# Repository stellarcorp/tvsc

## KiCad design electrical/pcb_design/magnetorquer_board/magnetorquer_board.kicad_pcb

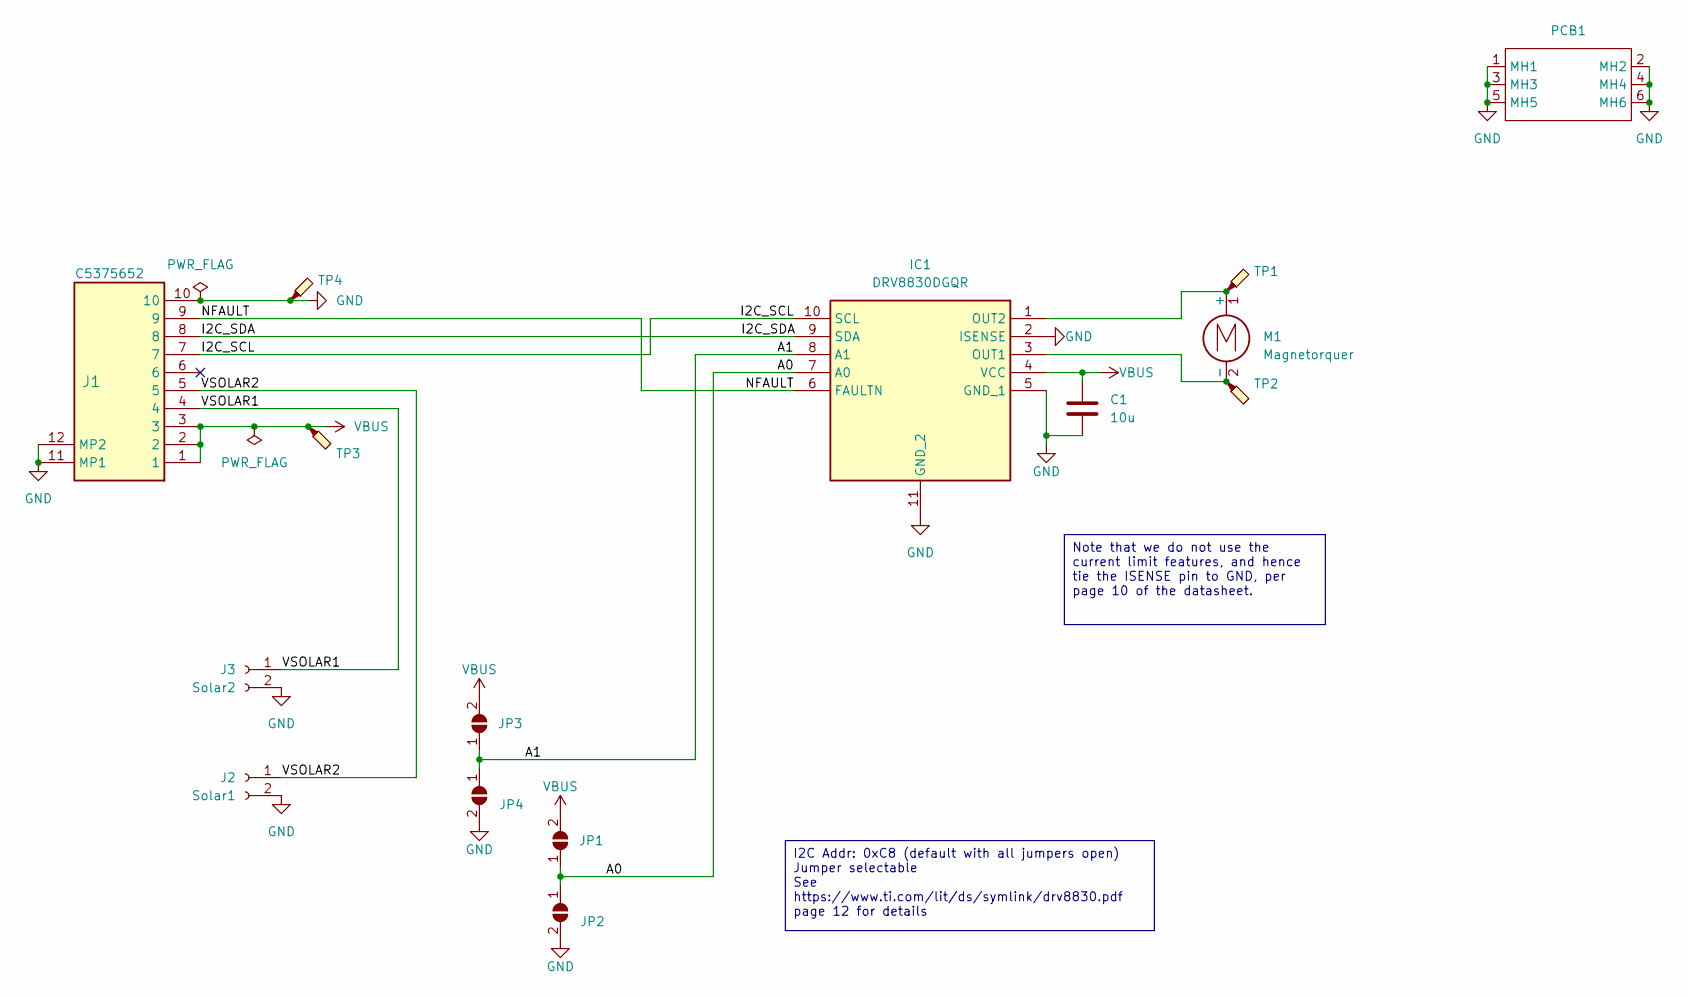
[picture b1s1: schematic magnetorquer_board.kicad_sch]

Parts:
C1: 10u; C_1206_3216Metric; MPN C77093
IC1: DRV8830DGQR; SOP50P490X110-11N; MPN C127591
J1: Molex_504050-0891; Molex_504050-1091; MPN C5375652
J2: Solar1; Solar Panel Connector (Raw Pads); MPN NA
J3: Solar2; Solar Panel Connector (Raw Pads); MPN NA
JP1, JP2, JP3, JP4: SolderJumper_2_Open; SolderJumper-2_P1.3mm_Open_RoundedPad1.0x1.5mm; MPN NA
M1: Magnetorquer; MPN NA
PCB1: Interior_Side_Panel_PCB_Shape; MPN NA
TP1, TP2, TP3, TP4: TestPoint_Probe; TestPoint_Pad_D1.5mm; MPN NA

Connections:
/A0: IC1.7 (A0), JP1.1 (A), JP2.1 (A)
/A1: IC1.8 (A1), JP3.1 (A), JP4.1 (A)
/I2C_SCL: IC1.10 (SCL), J1.7
/I2C_SDA: IC1.9 (SDA), J1.8
/NFAULT: IC1.6 (FAULTN), J1.9
/VSOLAR1: J1.4, J3.1
/VSOLAR2: J1.5, J2.1
GND: C1.2, IC1.2 (ISENSE), IC1.5 (GND_1), IC1.11 (GND_2), J1.10, J1.11 (MP1), J1.12 (MP2), J2.2, J3.2, JP2.2 (B), JP4.2 (B), PCB1.1 (MH1), PCB1.2 (MH2), PCB1.3 (MH3), PCB1.4 (MH4), PCB1.5 (MH5), PCB1.6 (MH6), TP4.1
unnamed: IC1.3 (OUT1), M1.2 (-), TP2.1
unnamed: IC1.1 (OUT2), M1.1 (+), TP1.1
VBUS: C1.1, IC1.4 (VCC), J1.1, J1.2, J1.3, JP1.2 (B), JP3.2 (B), TP3.1

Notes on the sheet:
Note that we do not use the current limit features, and hence tie the ISENSE pin to GND, per page 10 of the datasheet.
I2C Addr: 0xC8 (default with all jumpers open) Jumper selectable See https://www.ti.com/lit/ds/symlink/drv8830.pdf page 12 for details

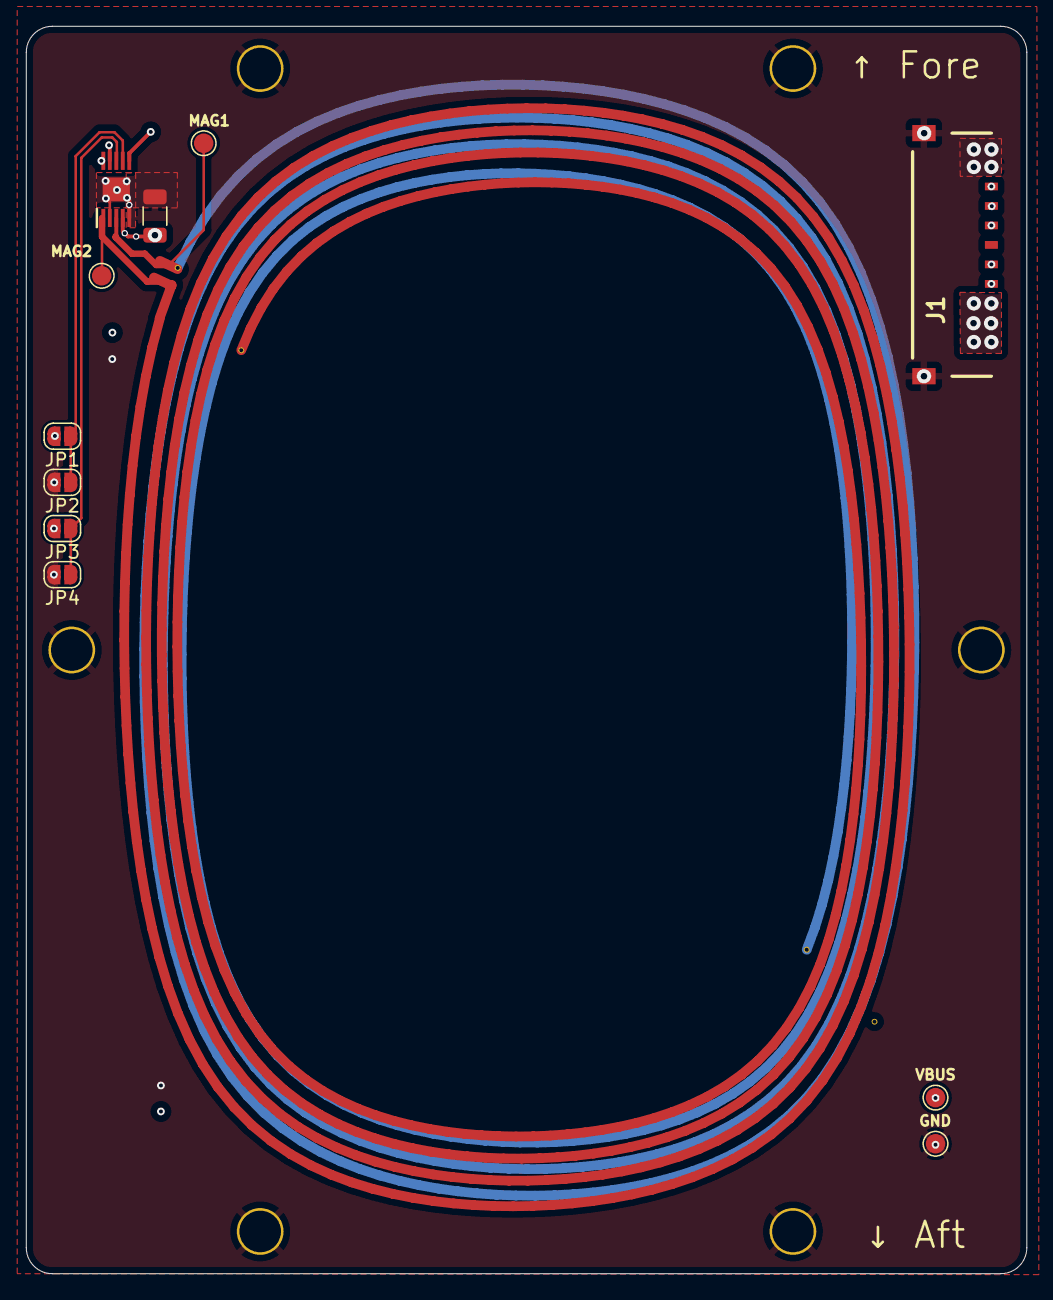
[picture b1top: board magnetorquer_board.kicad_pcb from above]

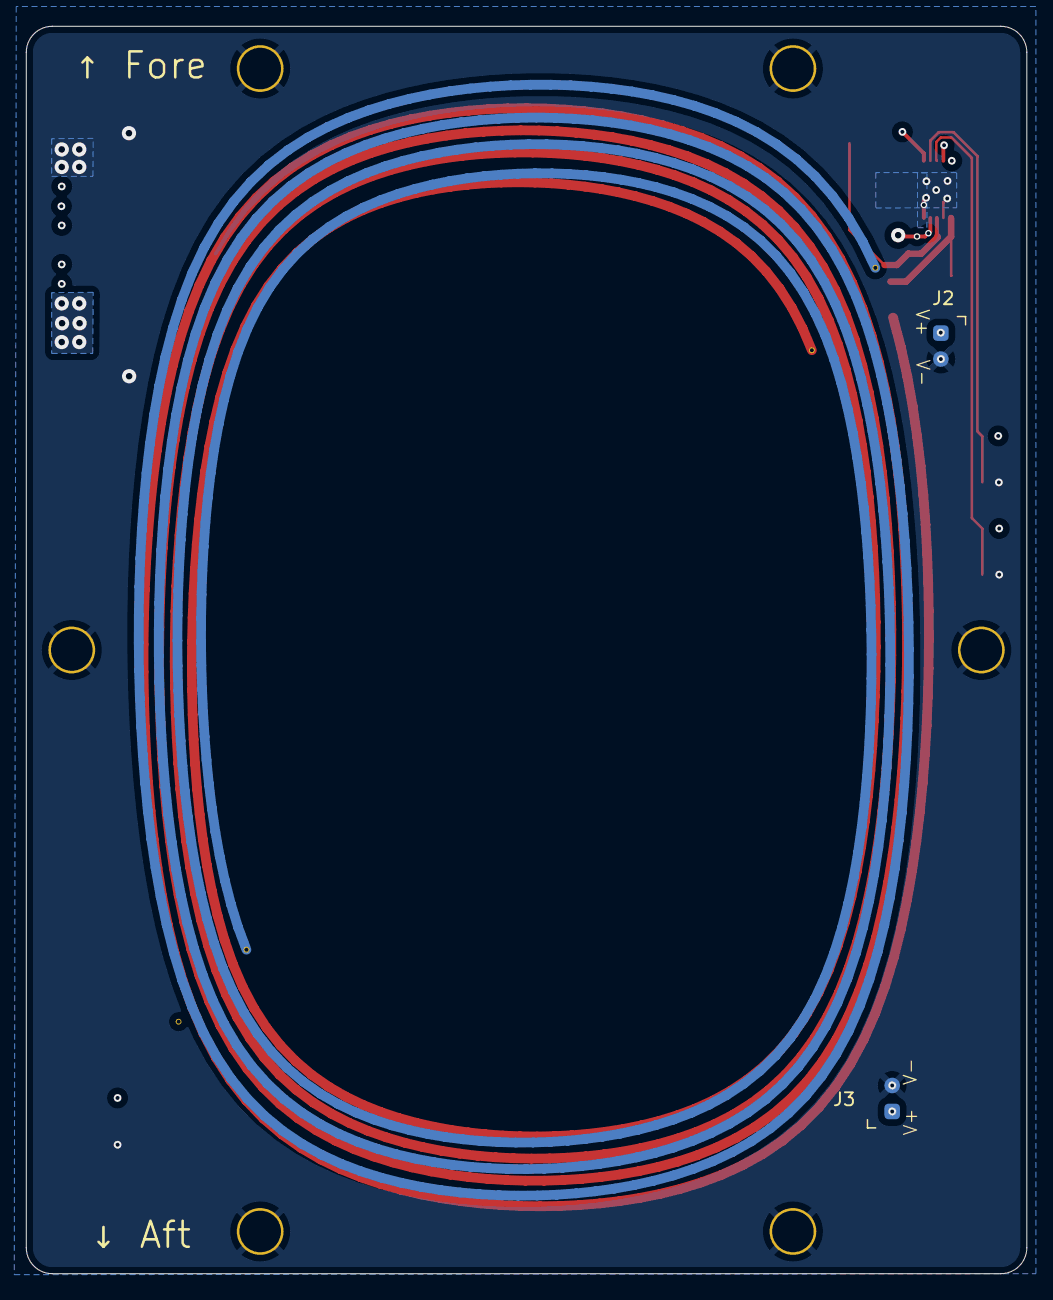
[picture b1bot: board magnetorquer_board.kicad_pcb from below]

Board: 4 copper layers, 77.0 x 96.0 mm, 15 parts (2 on the bottom side), 11 nets.

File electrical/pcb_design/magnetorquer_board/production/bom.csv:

Designator,Footprint,Quantity,Value,LCSC Part #
C1,1206,1,10u,C77093
IC1,SOP50P490X110-11N,1,DRV8830DGQR,C127591
J1,Molex_504050-0891,1,Molex_504050-0891,C587992
J2,Solar Panel Connector (Raw Pads),1,Solar1,NA
J3,Solar Panel Connector (Raw Pads),1,Solar2,NA
"JP1, JP2, JP3, JP4",SolderJumper-2_P1.3mm_Open_RoundedPad1.0x1.5mm,4,SolderJumper_2_Open,NA
M1,Magnetorquer,1,Magnetorquer,NA
"TP1, TP2, TP3, TP4",TestPoint_Pad_D1.5mm,4,TestPoint_Probe,NA

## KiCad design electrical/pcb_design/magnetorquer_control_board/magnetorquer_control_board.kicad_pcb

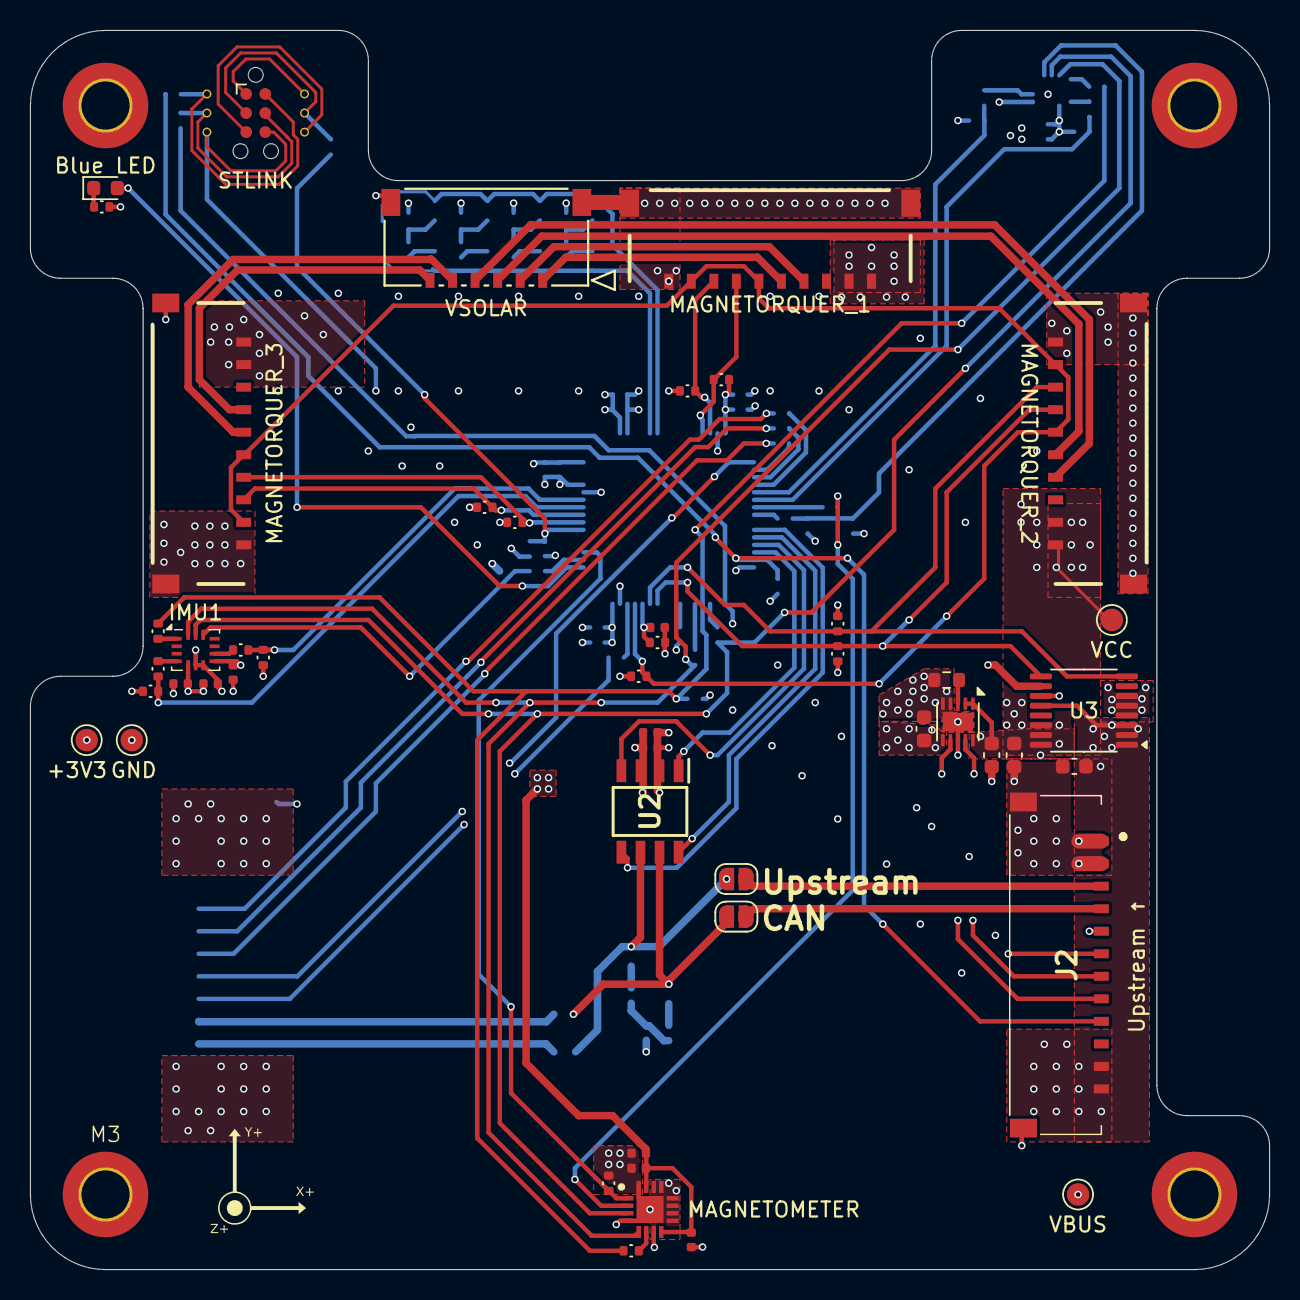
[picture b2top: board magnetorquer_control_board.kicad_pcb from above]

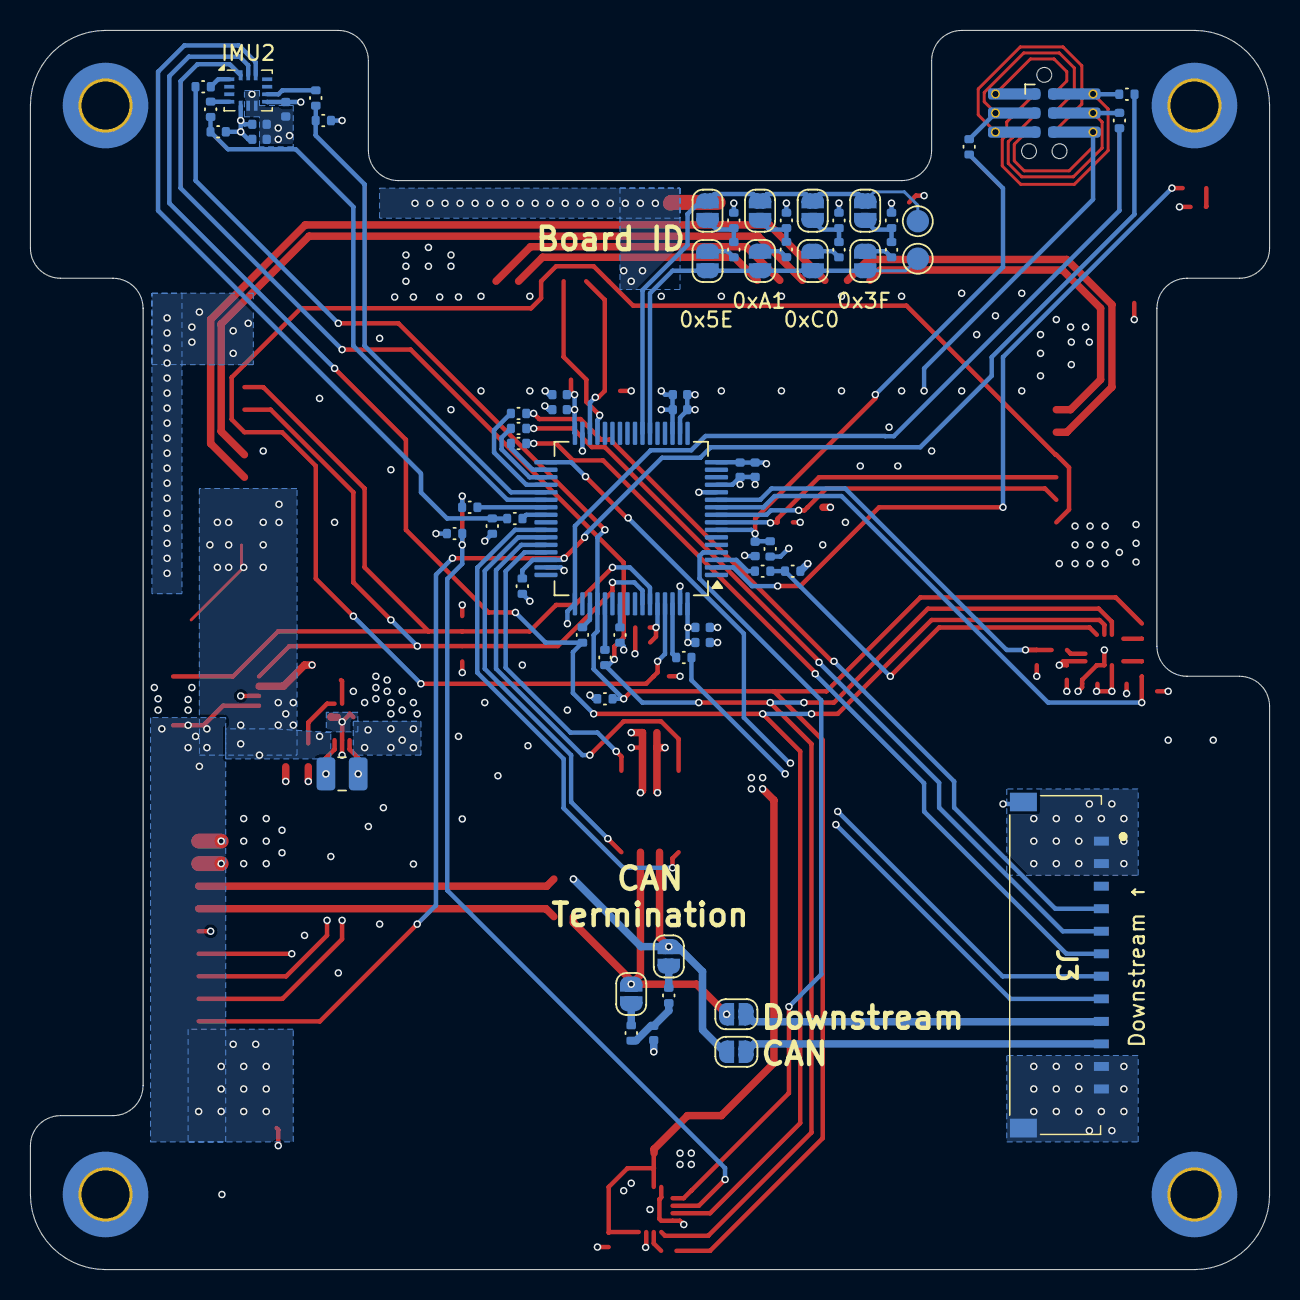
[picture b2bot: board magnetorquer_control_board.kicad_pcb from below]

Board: 4 copper layers, 82.5 x 82.5 mm, 114 parts (66 on the bottom side), 86 nets.

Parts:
C1, C2, C3, C7, C8, C9, C13, C14, C17, C18, C21, C22, C23, C25: 100n; Nondescript_C_0402_1005Metric
C4, C26: 10u; Nondescript_C_0603_1608Metric
C5, C27: 22u; Nondescript_C_0603_1608Metric
C10, C11, C12, C15, C16, C19, C20, C24: 1u; Nondescript_C_0402_1005Metric
D1: Blue LED; LED_0603_1608Metric
J1: STLINK; Double-Sided_Tag-Connect_TC2030-IDC-NL_2x03_P1.27mm_Vertical
J2: Molex_504050-1291; Bus Connector (Target)
J3: Molex_504050-1291; Bus Connector (Control)
J4: VSOLAR; Molex_504050-0691
J5: MAGNETORQUER_1; Molex_504050-1091
J6: MAGNETORQUER_2; Molex_504050-1091
J7: MAGNETORQUER_3; Molex_504050-1091
JP1, JP2, JP3, JP4, JP5, JP6: SolderJumper_2_Open; SolderJumper-2_P1.3mm_Open_RoundedPad1.0x1.5mm
JP7, JP11: 0x3F; SolderJumper-2_P1.3mm_Open_RoundedPad1.0x1.5mm
JP8, JP12: 0xC0; SolderJumper-2_P1.3mm_Open_RoundedPad1.0x1.5mm
JP9, JP13: 0xA1; SolderJumper-2_P1.3mm_Open_RoundedPad1.0x1.5mm
JP10, JP14: 0x5E; SolderJumper-2_P1.3mm_Open_RoundedPad1.0x1.5mm
L1: 2.2µH; L_1008_2520Metric
PCB1: Core_Board_Shape_Space_Invader_2
R1, R3, R6, R10, R11, R12, R13, R14, R15, R16, R22, R25, R29, R32, R33, R34, R35, R36, R44, R47, R48: 9k31; Nondescript_R_0402_1005Metric
R2, R4, R5, R7, R8, R9, R17, R18, R19, R20, R21, R23, R24, R26, R27, R28, R30, R31, R37, R38, R39: 33; Nondescript_R_0402_1005Metric
R40, R43: 18k7; Nondescript_R_0402_1005Metric
R41, R42: 6k19; Nondescript_R_0402_1005Metric
R45, R46: 15k8; Nondescript_R_0402_1005Metric
R49, R50: 60; Nondescript_R_0402_1005Metric
R51: 36k5; Nondescript_R_0603_1608Metric
TP1: VBUS; TestPoint_Pad_D1.5mm
TP2: VCC; TestPoint_Pad_D1.5mm
TP3: GND; TestPoint_Pad_D1.5mm
TP4: +3V3; TestPoint_Pad_D1.5mm
TP5: BOARD_ID_SENSE; TestPoint_Pad_D1.5mm
TP6: BOARD_ID_POWER; TestPoint_Pad_D1.5mm
U1: STM32L452RCTx; LQFP-64_10x10mm_P0.5mm
U2: TCAN330DR; SOIC127P600X175-8N
U3: INA260; TSSOP-16_4.4x5mm_P0.65mm
U5: MAGNETOMETER; QFN50P300X300X100-17N-D
U6: IMU1; Bosch_LGA-14_3x2.5mm_P0.5mm
U7: IMU2; Bosch_LGA-14_3x2.5mm_P0.5mm
U8: TPS63900; WSON-10-1EP_2.5x2.5mm_P0.5mm_EP1.2x2mm

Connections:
+3V3: C5.1, C7.1, C8.1, C9.1, C10.1, C11.1, C12.1, C13.1, C14.1, C15.1, C16.1, C17.1, C18.1, C19.1, C20.1, C21.1, C22.1, C23.1, C24.1, C25.1, J1.1 (T_VCC), R1.1, R6.1, R10.1, R11.1, R12.1, R13.1, R14.1, R15.1, R16.1, R22.1, R25.1, R29.1, R32.1, R33.1, R35.1, R36.1, R48.1, TP4.1, U1.13 (VDDA), U1.19 (VDD), U1.32 (VDD), U1.64 (VDD), U2.3 (VCC), U3.10 (VS), U5.8 (VDD_IO), U5.15 (VDD), U6.5 (VDDIO), U6.8 (VDD), U7.5 (VDDIO), U7.8 (VDD), U8.6 (VOUT)
/BOOT0: C2.1, J2.5 (BOOT0), R3.1, U1.60 (PH3)
/Board Identification/BOARD_ID_POWER: JP11.1 (A), JP12.1 (A), JP13.1 (A), JP14.1 (A), TP6.1, U1.22 (PA6)
/Board Identification/BOARD_ID_SENSE: JP7.1 (A), JP8.1 (A), JP9.1 (A), JP10.1 (A), TP5.1, U1.23 (PA7)
/CAN bus/CANH_TERMINATION: JP3.2 (B), R49.1
/CAN bus/CANL_TERMINATION: JP4.1 (A), R50.2
/CAN bus/CAN_RX: U1.44 (PA11), U2.4 (RXD)
/CAN bus/CAN_SHUTDOWN: U1.42 (PA9), U2.5 (SHDN)
/CAN bus/CAN_SILENT: U1.43 (PA10), U2.8 (S)
/CAN bus/CAN_TX: U1.45 (PA12), U2.1 (TXD)
/CANH_DOWNSTREAM: J3.9 (CANH), JP5.2 (B)
/CANH_UPSTREAM: J2.4 (CANH), JP1.1 (A)
/CANL_DOWNSTREAM: J3.10 (CANL), JP6.2 (B)
/CANL_UPSTREAM: J2.3 (CANL), JP2.1 (A)
/CTRL.BOOT0: J3.8 (BOOT0_CTRL), R7.2
/CTRL.NRST: J3.5 (NRST_CTRL), R5.2
/CTRL.SWCLK: J3.6 (SWCLK_CTRL), R8.2
/CTRL.SWDIO: J3.4 (SWDIO_CTRL), R9.2
/CTRL.SWO: J3.7 (SWO_CTRL), U1.33 (PB12)
/I2C1.SCL: J6.4, R12.2, U1.58 (PB6), U3.9 (SCL)
/I2C1.SDA: J6.3, R11.2, U1.59 (PB7), U3.8 (SDA)
/I2C2.SCL: J5.4, R14.2, U1.29 (PB10)
/I2C2.SDA: J5.3, R13.2, U1.30 (PB11)
/I2C3.SCL: J7.4, R16.2, U1.8 (PC0)
/I2C3.SDA: J7.3, R15.2, U1.9 (PC1)
/IMU/IMU1_INT1: R26.2, R35.2, U1.10 (PC2)
/IMU/IMU1_INT2: R27.2, R32.2, U1.11 (PC3)
/IMU/IMU1_SPI_CS: R21.1, R48.2, U6.12 (CSB)
/IMU/IMU2_INT1: R30.2, R36.2, U1.38 (PC7)
/IMU/IMU2_INT2: R31.2, R33.2, U1.37 (PC6)
/IMU/IMU2_SPI_CS: R20.1, R29.2, U7.12 (CSB)
/IMU/IMU_MAG_INT1: R34.1, U1.4 (PC15), U5.1 (INT)
/IMU/IMU_MAG_SPI_CS: R17.1, R25.2, U5.2 (SENB/CS)
/MCU/DEBUG_LED: D1.2 (A), U1.2 (PC13)
/MCU/NMAG_FAULT: J5.2, J5.5, J6.2, J6.5, J7.2, J7.5, R10.2, U1.61 (PB8)
/Magnetorquer Control/VSOLAR_1_1: J4.1, J5.6
/Magnetorquer Control/VSOLAR_1_2: J4.2, J5.7
/Magnetorquer Control/VSOLAR_2_1: J4.3, J6.6
/Magnetorquer Control/VSOLAR_2_2: J4.4, J6.7
/Magnetorquer Control/VSOLAR_3_1: J4.5, J7.6
/Magnetorquer Control/VSOLAR_3_2: J4.6, J7.7
/NRST: C1.1, J2.8 (NRST), R1.2, R37.1, U1.7 (NRST)
/SPI3.MISO: R22.2, R23.2, R24.1, R28.2, U1.52 (PC11)
/SPI3.MOSI: R19.1, U5.5 (SDA/MOSI), U6.14 (SDx), U7.14 (SDx)
/SPI3.SCK: R18.1, U5.3 (SCL/SCLK), U6.13 (SCx), U7.13 (SCx)
/SWCLK: J2.7 (SWCLK), R39.1, U1.49 (PA14)
/SWDIO: J2.9 (SWDIO), R6.2, R38.1, U1.46 (PA13)
/SWO: J1.6 (T_SWO), J2.6 (SWO), R4.2
GND: C1.2, C2.2, C3.1, C4.2, C5.2, C7.2, C8.2, C9.2, C10.2, C11.2, C12.2, C13.2, C14.2, C15.2, C16.2, C17.2, C18.2, C19.2, C20.2, C21.2, C22.2, C23.2, C24.2, C25.2, C26.2, C27.2, J1.5 (GND), J2.1 (GND), J2.2 (GND), J2.MP1, J2.MP2, J3.11 (GND), J3.12 (GND), J3.MP1, J3.MP2, J4.7 (MP1), J4.8 (MP2), J5.1, J5.11 (MP1), J5.12 (MP2), J6.1, J6.11 (MP1), J6.12 (MP2), J7.1, J7.11 (MP1), J7.12 (MP2), PCB1.MH1, PCB1.MH2, PCB1.MH3, PCB1.MH4, R2.2, R3.2, R34.2, R41.2, R43.2, R45.1, R47.1, R51.2, TP3.1, U1.12 (VSSA), U1.16 (PA2), U1.18 (VSS), U1.31 (VSS), U1.47 (VSS), U1.63 (VSS), U2.2 (GND), U3.4 (A1), U3.5 (A0), U3.6 (GND), U3.11 (GND), U5.4 (N/C_1), U5.7 (INT/TRIG), U5.9 (N/C_2), U5.10 (N/C_3), U5.11 (A1), U5.12 (A0), U5.13 (VSS), U5.14 (N/C_4), U5.16 (N/C_5), U5.17 (EP), U6.6 (GNDIO), U6.7 (GND), U7.6 (GNDIO), U7.7 (GND), U8.4 (CFG2), U8.5 (CFG3), U8.8 (GND), U8.11 (GND)
unnamed: C3.2, R49.2, R50.1
unnamed: D1.1 (K), R2.1
unnamed: J1.3 (T_NRST), R37.2
unnamed: J1.4 (T_SWCLK), R39.2
unnamed: J1.2 (T_SWDIO), R38.2
unnamed: JP1.2 (B), JP3.1 (A), JP5.1 (A), U2.7 (CANH)
unnamed: JP2.2 (B), JP4.2 (B), JP6.1 (A), U2.6 (CANL)
unnamed: JP7.2 (B), R40.2, R41.1
unnamed: JP8.2 (B), R42.2, R43.1
unnamed: JP9.2 (B), R44.1, R45.2
unnamed: JP10.2 (B), R46.1, R47.2
unnamed: JP11.2 (B), R40.1
unnamed: JP12.2 (B), R42.1
unnamed: JP13.2 (B), R44.2
unnamed: JP14.2 (B), R46.2
unnamed: R4.1, U1.55 (PB3)
unnamed: R7.1, U1.62 (PB9)
unnamed: R8.1, U1.34 (PB13)
unnamed: R5.1, U1.35 (PB14)
unnamed: R9.1, U1.36 (PB15)
unnamed: R17.2, U1.39 (PC8)
unnamed: R20.2, U1.40 (PC9)
unnamed: R18.2, U1.51 (PC10)
unnamed: R19.2, U1.53 (PC12)
unnamed: R21.2, U1.3 (PC14)
unnamed: R23.1, U5.6 (MISO)
unnamed: R26.1, U6.4 (INT1)
unnamed: R27.1, U6.9 (INT2)
unnamed: R24.2, U6.1 (SDO)
unnamed: R30.1, U7.4 (INT1)
unnamed: R31.1, U7.9 (INT2)
unnamed: R28.1, U7.1 (SDO)
unnamed: R51.1, U8.3 (CFG1)
unnamed: L1.2, U8.9 (LX1)
unnamed: L1.1, U8.7 (LX2)
VBUS: C4.1, J2.11 (VBUS), J2.12 (VBUS), J3.1 (VBUS), J3.2 (VBUS), TP1.1, U3.1 (IN+), U3.2 (IN+), U3.3 (IN+), U3.12 (VBUS)
VCC: C26.1, C27.1, J5.9, J5.10, J6.9, J6.10, J7.9, J7.10, TP2.1, U3.14 (IN-), U3.15 (IN-), U3.16 (IN-), U8.1 (EN), U8.2 (SEL), U8.10 (VIN)

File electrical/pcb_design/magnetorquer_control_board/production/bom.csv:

Designator,Footprint,Quantity,Value,LCSC Part #
"C1, C13, C14, C17, C18, C2, C21, C22, C23, C25, C3, C7, C8, C9",Nondescript_C_0402_1005Metric,14,100n,C1525
"C10, C11, C12, C15, C16, C19, C20, C24",Nondescript_C_0402_1005Metric,8,1u,C52923
"C26, C4",Nondescript_C_0603_1608Metric,2,10u,C77041
"C27, C5",Nondescript_C_0603_1608Metric,2,22u,C710887
D1,0603,1,Blue LED,C72041
J2,Bus Connector (Target),1,Molex_504050-1291,C563982
J3,Bus Connector (Control),1,Molex_504050-1291,C563982
J4,Molex_504050-0691,1,VSOLAR,C563981
J5,Molex_504050-1091,1,MAGNETORQUER_1,C5375652
J6,Molex_504050-1091,1,MAGNETORQUER_2,C5375652
J7,Molex_504050-1091,1,MAGNETORQUER_3,C5375652
L1,1008,1,2.2µH,C576403
"R1, R10, R11, R12, R13, R14, R15, R16, R22, R25, R29, R3, R32, R33, R34, R35, R36, R44, R47, R48, R6",Nondescript_R_0402_1005Metric,21,9k31,C270572
"R17, R18, R19, R2, R20, R21, R23, R24, R26, R27, R28, R30, R31, R37, R38, R39, R4, R5, R7, R8, R9",Nondescript_R_0402_1005Metric,21,33,C25105
"R40, R43",Nondescript_R_0402_1005Metric,2,18k7,C11476
"R41, R42",Nondescript_R_0402_1005Metric,2,6k19,C25914
"R45, R46",Nondescript_R_0402_1005Metric,2,15k8,C26956
"R49, R50",Nondescript_R_0402_1005Metric,2,60,C60310
R51,Nondescript_R_0603_1608Metric,1,36k5,C23029
U1,LQFP-64_10x10mm_P0.5mm,1,STM32L452RCTx,C192722
U2,SOIC127P600X175-8N,1,TCAN330DR,C2652876
U3,TSSOP-16_4.4x5mm_P0.65mm,1,INA260,C2155885
U5,QFN50P300X300X100-17N-D,1,MAGNETOMETER,C2654971
U6,Bosch_LGA-14_3x2.5mm_P0.5mm,1,IMU1,C5368700
U7,Bosch_LGA-14_3x2.5mm_P0.5mm,1,IMU2,C5368700
U8,WSON-10-1EP_2.5x2.5mm_P0.5mm_EP1.2x2mm,1,TPS63900,C1518762

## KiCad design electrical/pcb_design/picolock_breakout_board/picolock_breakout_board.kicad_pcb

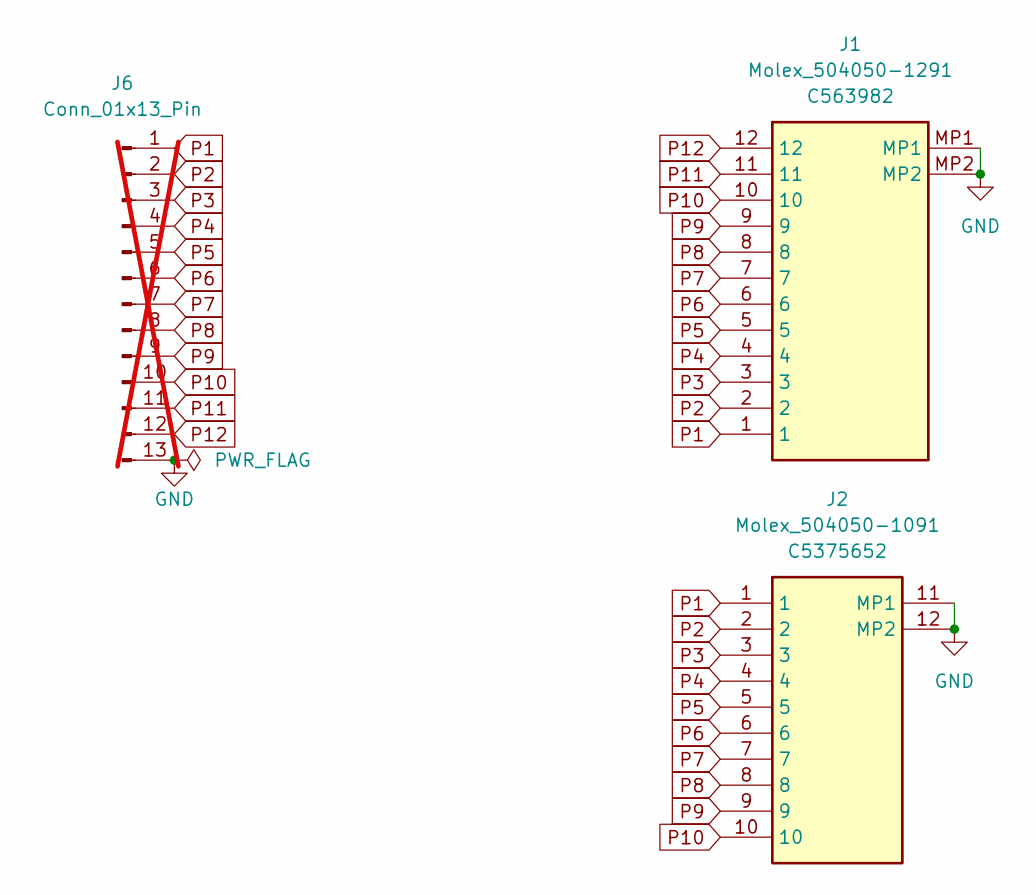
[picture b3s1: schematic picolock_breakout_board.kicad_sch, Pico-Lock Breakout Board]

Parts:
J1: Molex_504050-1291; Manufacturer Part Number 504050-1291
J2: Molex_504050-1091; Manufacturer Part Number 504050-1091
J6: Conn_01x13_Pin; PinHeader_1x13_P2.54mm_Vertical; not fitted

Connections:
GND: J1.MP1, J1.MP2, J2.11 (MP1), J2.12 (MP2), J6.13
P1: J1.1, J2.1, J6.1
P2: J1.2, J2.2, J6.2
P3: J1.3, J2.3, J6.3
P4: J1.4, J2.4, J6.4
P5: J1.5, J2.5, J6.5
P6: J1.6, J2.6, J6.6
P7: J1.7, J2.7, J6.7
P8: J1.8, J2.8, J6.8
P9: J1.9, J2.9, J6.9
P10: J1.10, J2.10, J6.10
P11: J1.11, J6.11
P12: J1.12, J6.12

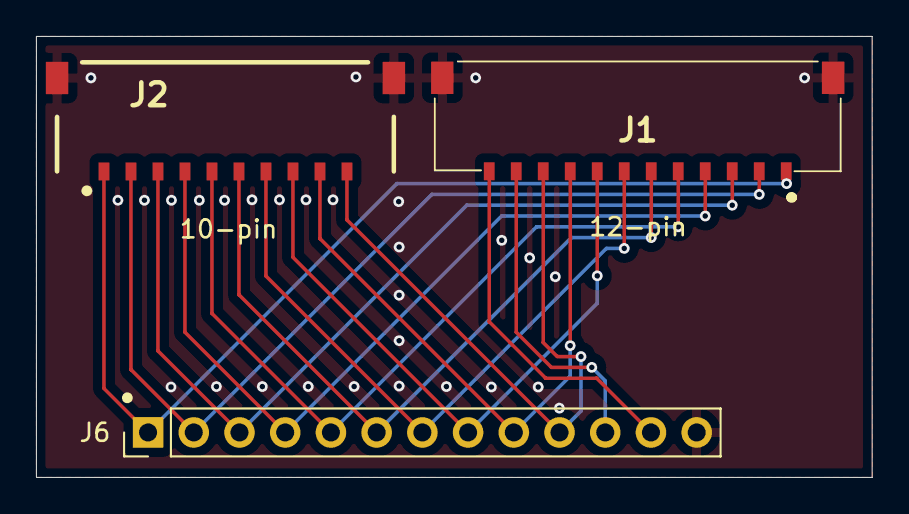
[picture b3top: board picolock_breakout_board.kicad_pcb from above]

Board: 2 copper layers, 46.4 x 24.5 mm, 3 parts (0 on the bottom side), 13 nets.

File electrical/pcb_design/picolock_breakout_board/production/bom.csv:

Designator,Footprint,Quantity,Value,LCSC Part #
J1,Molex_504050-1291,1,Molex_504050-1291,C563982
J2,Molex_504050-1091,1,Molex_504050-1091,C5375652

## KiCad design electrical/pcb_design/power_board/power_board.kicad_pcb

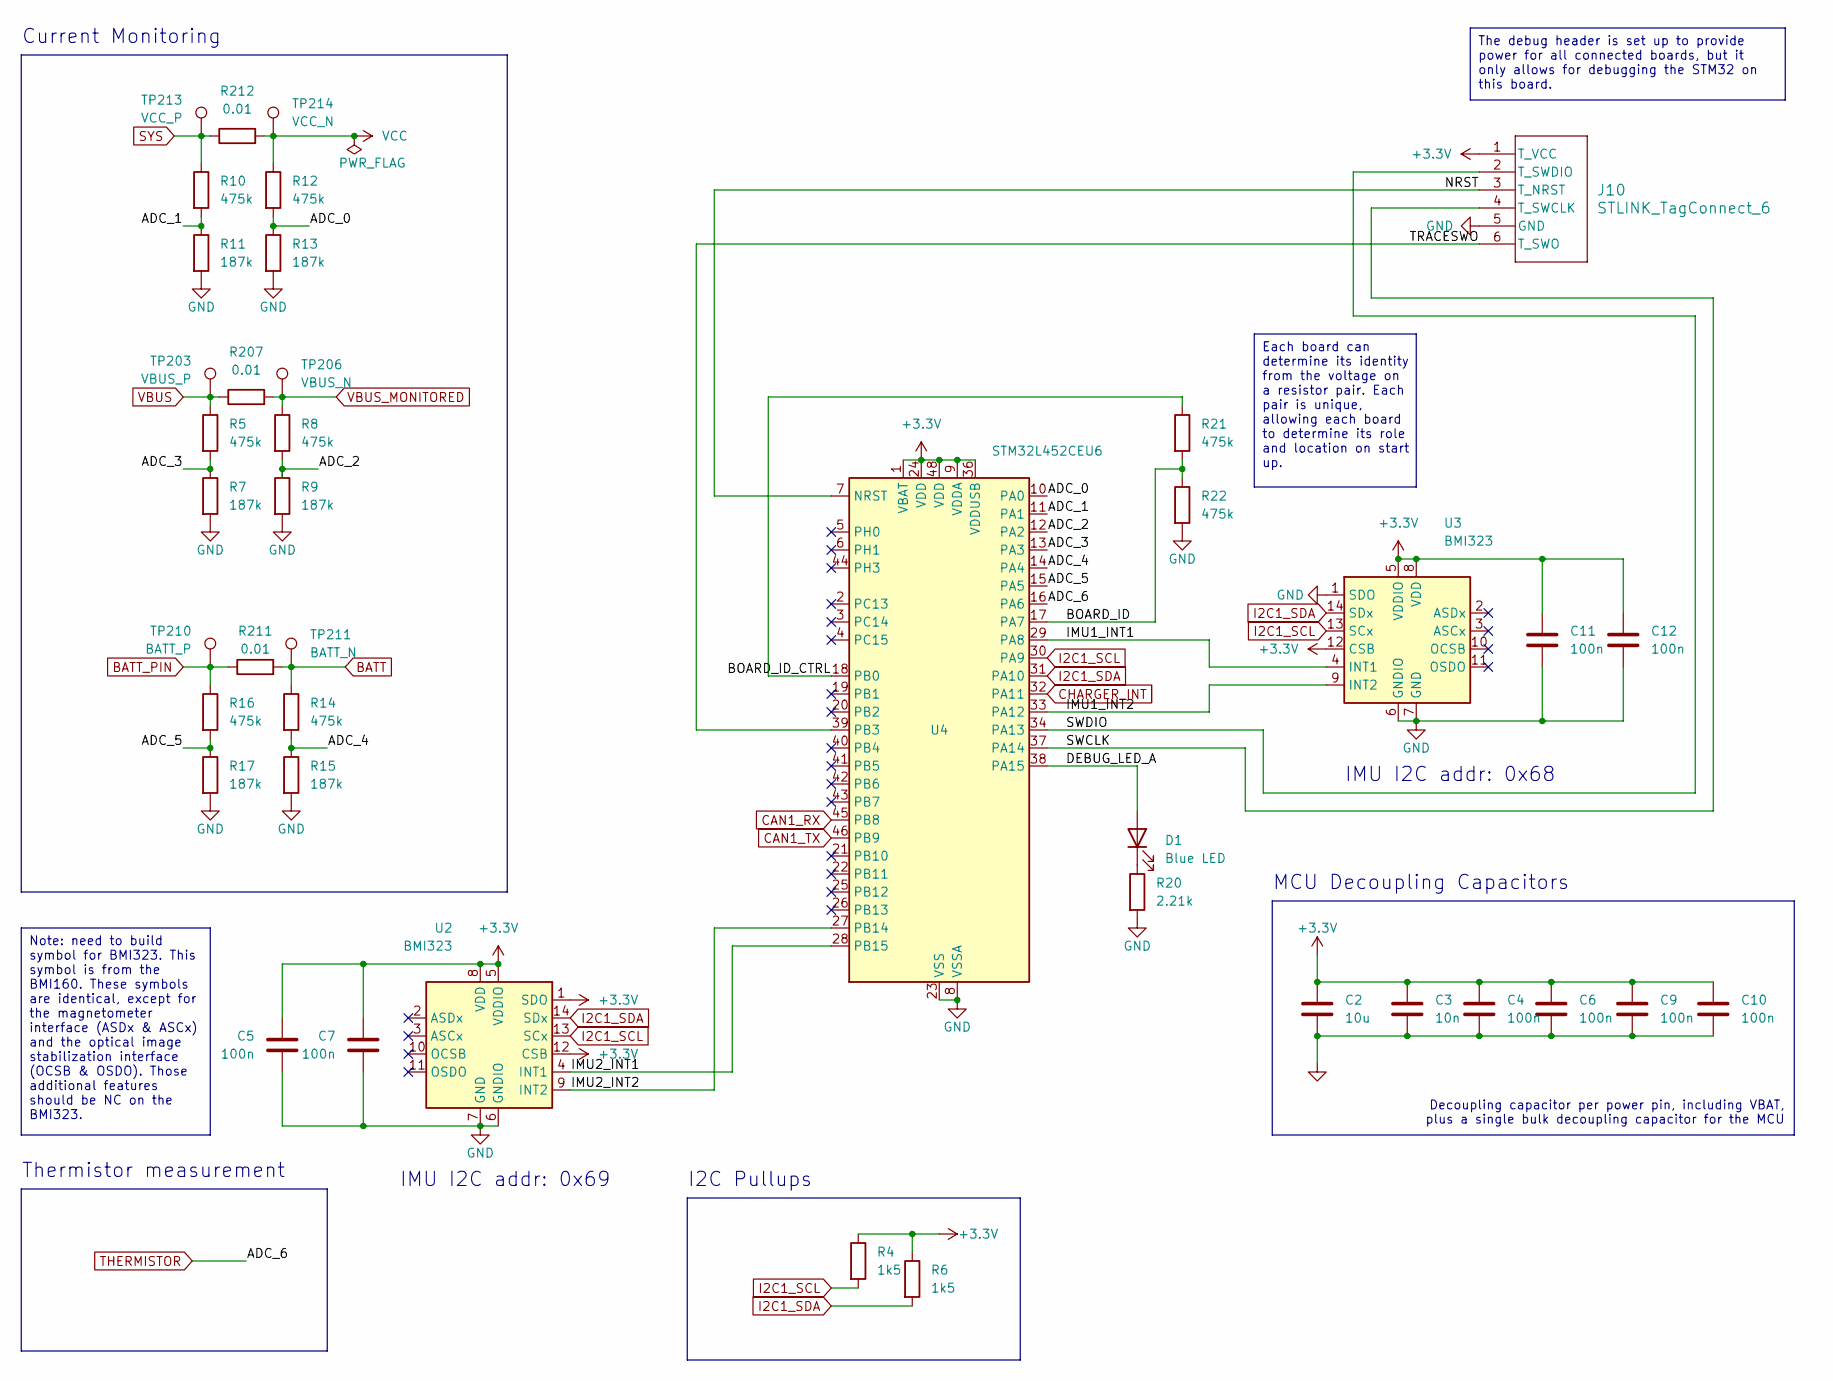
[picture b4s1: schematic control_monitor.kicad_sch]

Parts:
C2: 10u; Nondescript_C_0603_1608Metric; MPN C344022
C3: 10n; Nondescript_C_0402_1005Metric; MPN C5189696
C4, C6, C9, C10: 100n; Nondescript_C_0402_1005Metric; MPN C2649549
C5, C7, C11, C12: 100n; Nondescript_C_0402_1005Metric; Manufacturer Part Number GCM155R71H104KE02J
D1: Blue LED; LED_0603_1608Metric; MPN C72041
J10: STLINK_TagConnect_6; Tag-Connect_TC2030-IDC-NL_2x03_P1.27mm_Vertical
R4, R6: 1k5; R_0402_1005Metric; MPN C25867
R5, R8, R10, R12, R14, R16, R21, R22: 475k; Nondescript_R_0402_1005Metric; MPN C25791
R7, R9, R11, R13, R15, R17: 187k; Nondescript_R_0402_1005Metric; MPN C25761
R20: 2.21k; Nondescript_R_0402_1005Metric; MPN C305298
R207, R211, R212: 0.01; R_2512_6332Metric; MPN C844296
TP203: VBUS_P; TestPoint_Pad_D2.5mm
TP206: VBUS_N; TestPoint_Pad_D2.5mm
TP210: BATT_P; TestPoint_Pad_D2.5mm
TP211: BATT_N; TestPoint_Pad_D2.5mm
TP213: VCC_P; TestPoint_Pad_D2.5mm
TP214: VCC_N; TestPoint_Pad_D2.5mm
U2, U3: BMI323; Bosch_LGA-14_3x2.5mm_P0.5mm; MPN C5368700
U4: STM32L452CEU6; QFN-48-1EP_7x7mm_P0.5mm_EP5.6x5.6mm_ThermalVias; MPN C222355

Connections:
+3.3V: C2.1, C3.1, C4.1, C5.1, C6.1, C7.1, C9.1, C10.1, C11.1, C12.1, J10.1 (T_VCC), R4.1, R6.1, U2.1 (SDO), U2.5 (VDDIO), U2.8 (VDD), U2.12 (CSB), U3.5 (VDDIO), U3.8 (VDD), U3.12 (CSB), U4.1 (VBAT), U4.9 (VDDA), U4.24 (VDD), U4.36 (VDDUSB), U4.48 (VDD); also elsewhere on the board
/Control & Monitoring/ADC_0: R12.2, R13.1, U4.10 (PA0)
/Control & Monitoring/ADC_1: R10.2, R11.1, U4.11 (PA1)
/Control & Monitoring/ADC_2: R8.2, R9.1, U4.12 (PA2)
/Control & Monitoring/ADC_3: R5.2, R7.1, U4.13 (PA3)
/Control & Monitoring/ADC_4: R14.2, R15.1, U4.14 (PA4)
/Control & Monitoring/ADC_5: R16.2, R17.1, U4.15 (PA5)
/Control & Monitoring/BOARD_ID: R21.2, R22.1, U4.17 (PA7)
/Control & Monitoring/BOARD_ID_CTRL: R21.1, U4.18 (PB0)
/Control & Monitoring/DEBUG_LED_A: D1.2 (A), U4.38 (PA15)
/Control & Monitoring/IMU1_INT1: U3.4 (INT1), U4.29 (PA8)
/Control & Monitoring/IMU1_INT2: U3.9 (INT2), U4.33 (PA12)
/Control & Monitoring/IMU2_INT1: U2.4 (INT1), U4.28 (PB15)
/Control & Monitoring/IMU2_INT2: U2.9 (INT2), U4.27 (PB14)
/Control & Monitoring/NRST: J10.3 (T_NRST), U4.7 (NRST)
/Control & Monitoring/SWCLK: J10.4 (T_SWCLK), U4.37 (PA14)
/Control & Monitoring/SWDIO: J10.2 (T_SWDIO), U4.34 (PA13)
/Control & Monitoring/TRACESWO: J10.6 (T_SWO), U4.39 (PB3)
BATT: R14.1, R211.2, TP211.1; also elsewhere on the board
BATT_PIN: R16.1, R211.1, TP210.1; also elsewhere on the board
CAN1_RX: U4.45 (PB8); also elsewhere on the board
CAN1_TX: U4.46 (PB9); also elsewhere on the board
CHARGER_INT: U4.32 (PA11); also elsewhere on the board
GND: C2.2, C3.2, C4.2, C5.2, C6.2, C7.2, C9.2, C10.2, C11.2, C12.2, J10.5 (GND), R7.2, R9.2, R11.2, R13.2, R15.2, R17.2, R20.2, R22.2, U2.6 (GNDIO), U2.7 (GND), U3.1 (SDO), U3.6 (GNDIO), U3.7 (GND), U4.8 (VSSA), U4.23 (VSS), U4.35 (VSS), U4.47 (VSS), U4.49 (VSS); also elsewhere on the board
I2C1_SCL: R4.2, U2.13 (SCx), U3.13 (SCx), U4.30 (PA9); also elsewhere on the board
I2C1_SDA: R6.2, U2.14 (SDx), U3.14 (SDx), U4.31 (PA10); also elsewhere on the board
unnamed: D1.1 (K), R20.1
SYS: R10.1, R212.1, TP213.1; also elsewhere on the board
THERMISTOR: U4.16 (PA6); also elsewhere on the board
VBUS: R5.1, R207.1, TP203.1; also elsewhere on the board
VBUS_MONITORED: R8.1, R207.2, TP206.1; also elsewhere on the board
VCC: R12.1, R212.2, TP214.1; also elsewhere on the board

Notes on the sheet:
Each board can determine its identity from the voltage on a resistor pair. Each pair is unique, allowing each board to determine its role and location on start up.
The debug header is set up to provide power for all connected boards, but it only allows for debugging the STM32 on this board.
Note: need to build symbol for BMI323. This symbol is from the BMI160. These symbols are identical, except for the magnetometer interface (ASDx & ASCx) and the optical image stabilization interface (OCSB & OSDO). Those additional features should be NC on the BMI323.
Decoupling capacitor per power pin, including VBAT, plus a single bulk decoupling capacitor for the MCU
IMU I2C addr: 0x69
Current Monitoring
MCU Decoupling Capacitors
Thermistor measurement
I2C Pullups
IMU I2C addr: 0x68
